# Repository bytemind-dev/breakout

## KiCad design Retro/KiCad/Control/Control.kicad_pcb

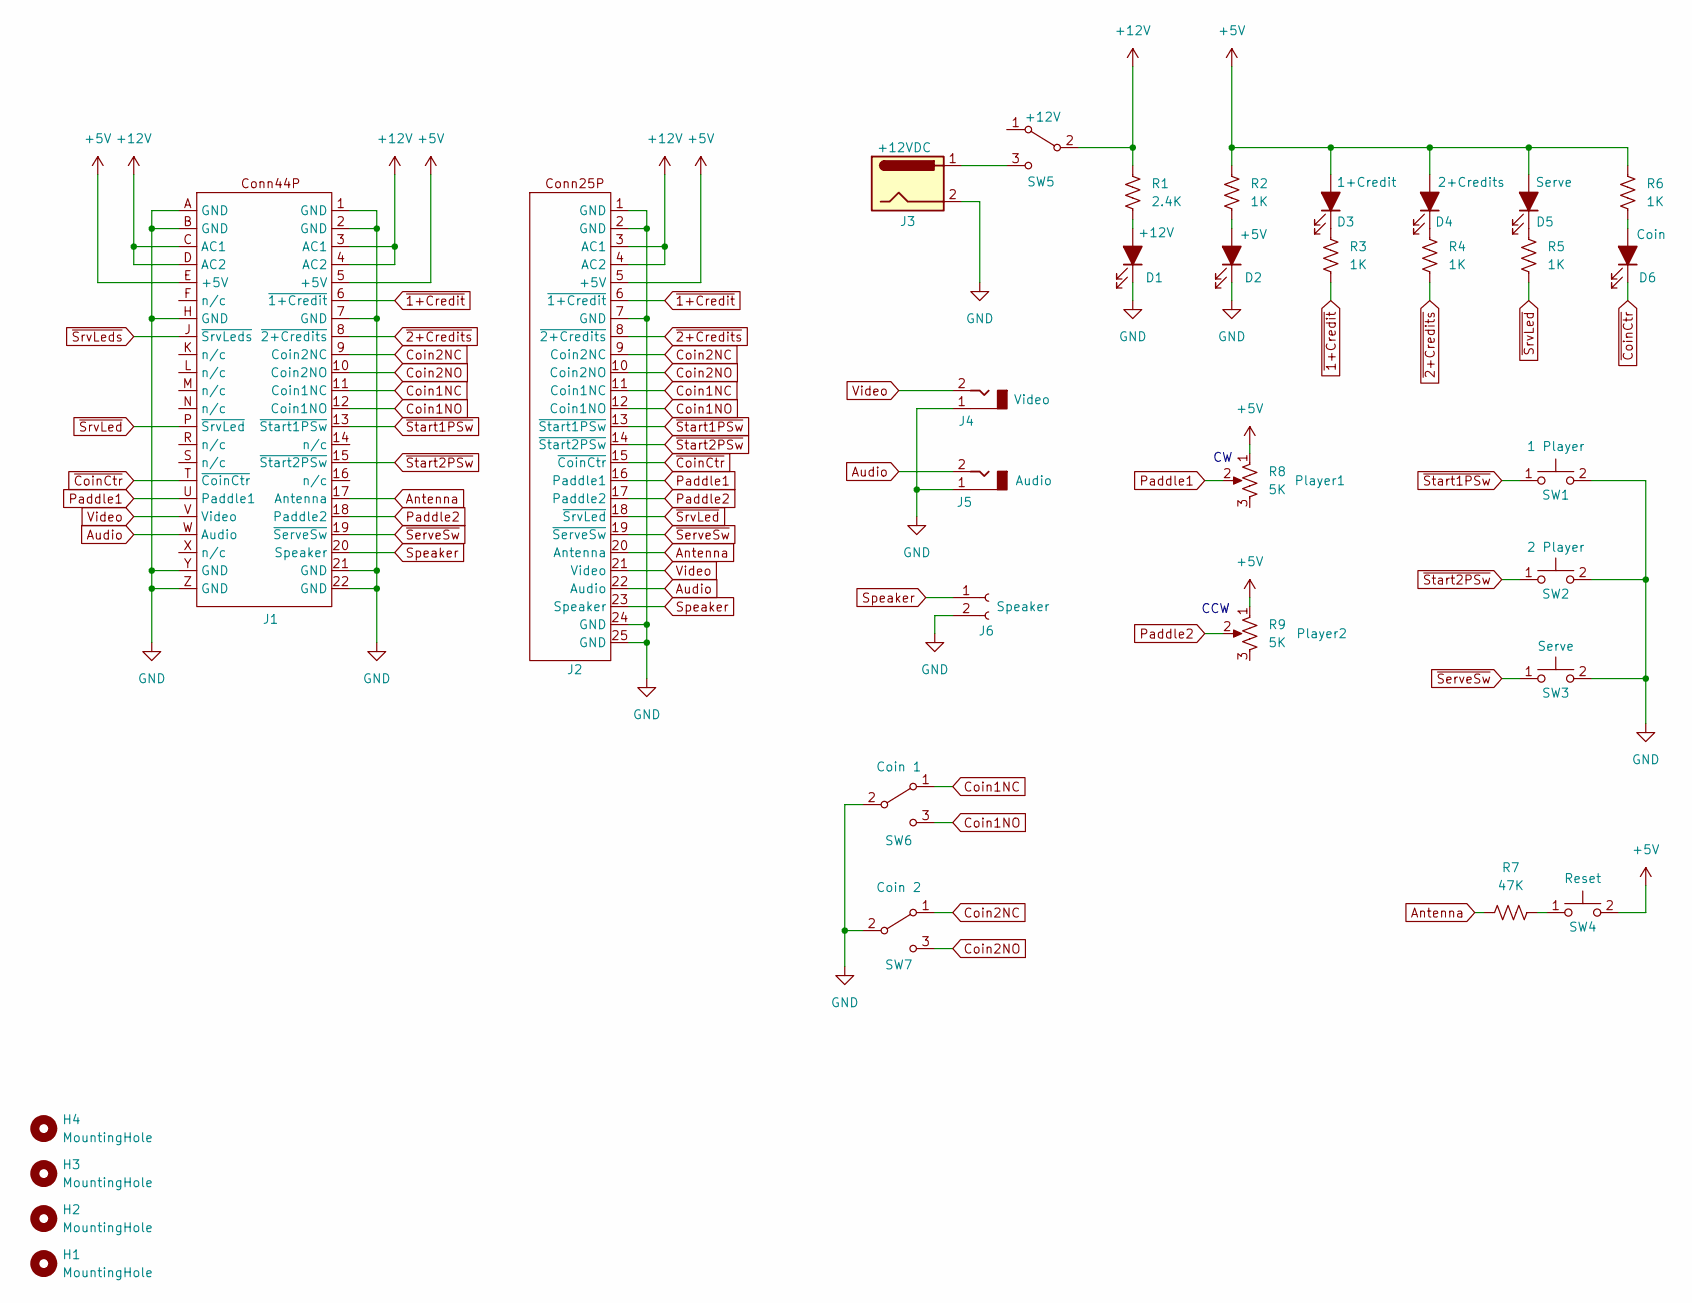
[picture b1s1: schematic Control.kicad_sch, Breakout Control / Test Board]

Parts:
D1: +12V; LED_D5.0mm
D2: +5V; LED_D5.0mm
D3: 1+Credit; LED_D5.0mm
D4: 2+Credits; LED_D5.0mm
D5: Serve; LED_D5.0mm
D6: Coin; LED_D5.0mm
H1, H2, H3, H4: MountingHole; Hole_4.3mm_M4
J1: Conn44F
J2: Conn_Head_1x25_P2.54mm_Vert
J3: Jack-DC; BarrelJack_Horizontal
J4: Video; CUI_RCJ-045
J5: Audio; CUI_RCJ-045
J6: Conn-TermBlock-2P
R1: 2.4K; R_Axial_0.6in
R2, R3, R4, R5, R6: 1K; R_Axial_0.6in
R7: 47K; R_Axial_0.6in
R8, R9: 5K; R_POT_Bourns_PDB181-A
SW1, SW2, SW3, SW4: SW_Push; SW_TACT_6.5x4.5mm
SW5, SW6, SW7: SW_SPDT; SW_Toggle_Gemini_A

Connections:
+5V: D3.2 (A), D4.2 (A), D5.2 (A), J1.5 (+5V), J1.E (+5V), J2.5 (+5V), R2.1, R6.1, R8.1, R9.1, SW4.2 (D)
+12V: J1.3 (AC1), J1.4 (AC2), J1.C (AC1), J1.D (AC2), J2.3 (AC1), J2.4 (AC2), R1.1, SW5.2 (B)
Antenna: J1.17 (Antenna), J2.20 (Antenna), R7.1
Audio: J1.W (Audio), J2.22 (Audio), J5.2
Coin1NC: J1.11 (Coin1NC), J2.11 (Coin1NC), SW6.1 (A)
Coin1NO: J1.12 (Coin1NO), J2.12 (Coin1NO), SW6.3 (C)
Coin2NC: J1.9 (Coin2NC), J2.9 (Coin2NC), SW7.1 (A)
Coin2NO: J1.10 (Coin2NO), J2.10 (Coin2NO), SW7.3 (C)
GND: D1.1 (K), D2.1 (K), J1.1 (GND), J1.2 (GND), J1.7 (GND), J1.21 (GND), J1.22 (GND), J1.A (GND), J1.B (GND), J1.H (GND), J1.Y (GND), J1.Z (GND), J2.1 (GND), J2.2 (GND), J2.7 (GND), J2.24 (GND), J2.25 (GND), J3.2, J4.1, J5.1, J6.2, SW1.2 (D), SW2.2 (D), SW3.2 (D), SW6.2 (B), SW7.2 (B)
unnamed: D1.2 (A), R1.2
unnamed: D2.2 (A), R2.2
unnamed: D3.1 (K), R3.1
unnamed: D4.1 (K), R4.1
unnamed: D5.1 (K), R5.1
unnamed: D6.2 (A), R6.2
unnamed: R7.2, SW4.1 (C)
unnamed: J3.1, SW5.3 (C)
Paddle1: J1.U (Paddle1), J2.16 (Paddle1), R8.2
Paddle2: J1.18 (Paddle2), J2.17 (Paddle2), R9.2
Speaker: J1.20 (Speaker), J2.23 (Speaker), J6.1
Video: J1.V (Video), J2.21 (Video), J4.2
~1+Credit: J1.6 (~1+Credit), J2.6 (~1+Credit), R3.2
~2+Credits: J1.8 (~2+Credits), J2.8 (~2+Credits), R4.2
~CoinCtr: D6.1 (K), J1.T (~CoinCtr), J2.15 (~CoinCtr)
~ServeSw: J1.19 (~ServeSw), J2.19 (~ServeSw), SW3.1 (C)
~SrvLeds: J1.J (~SrvLeds)
~SrvLed: J1.P (~SrvLed), J2.18 (~SrvLed), R5.2
~Start1PSw: J1.13 (~Start1PSw), J2.13 (~Start1PSw), SW1.1 (C)
~Start2PSw: J1.15 (~Start2PSw), J2.14 (~Start2PSw), SW2.1 (C)

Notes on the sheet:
CCW

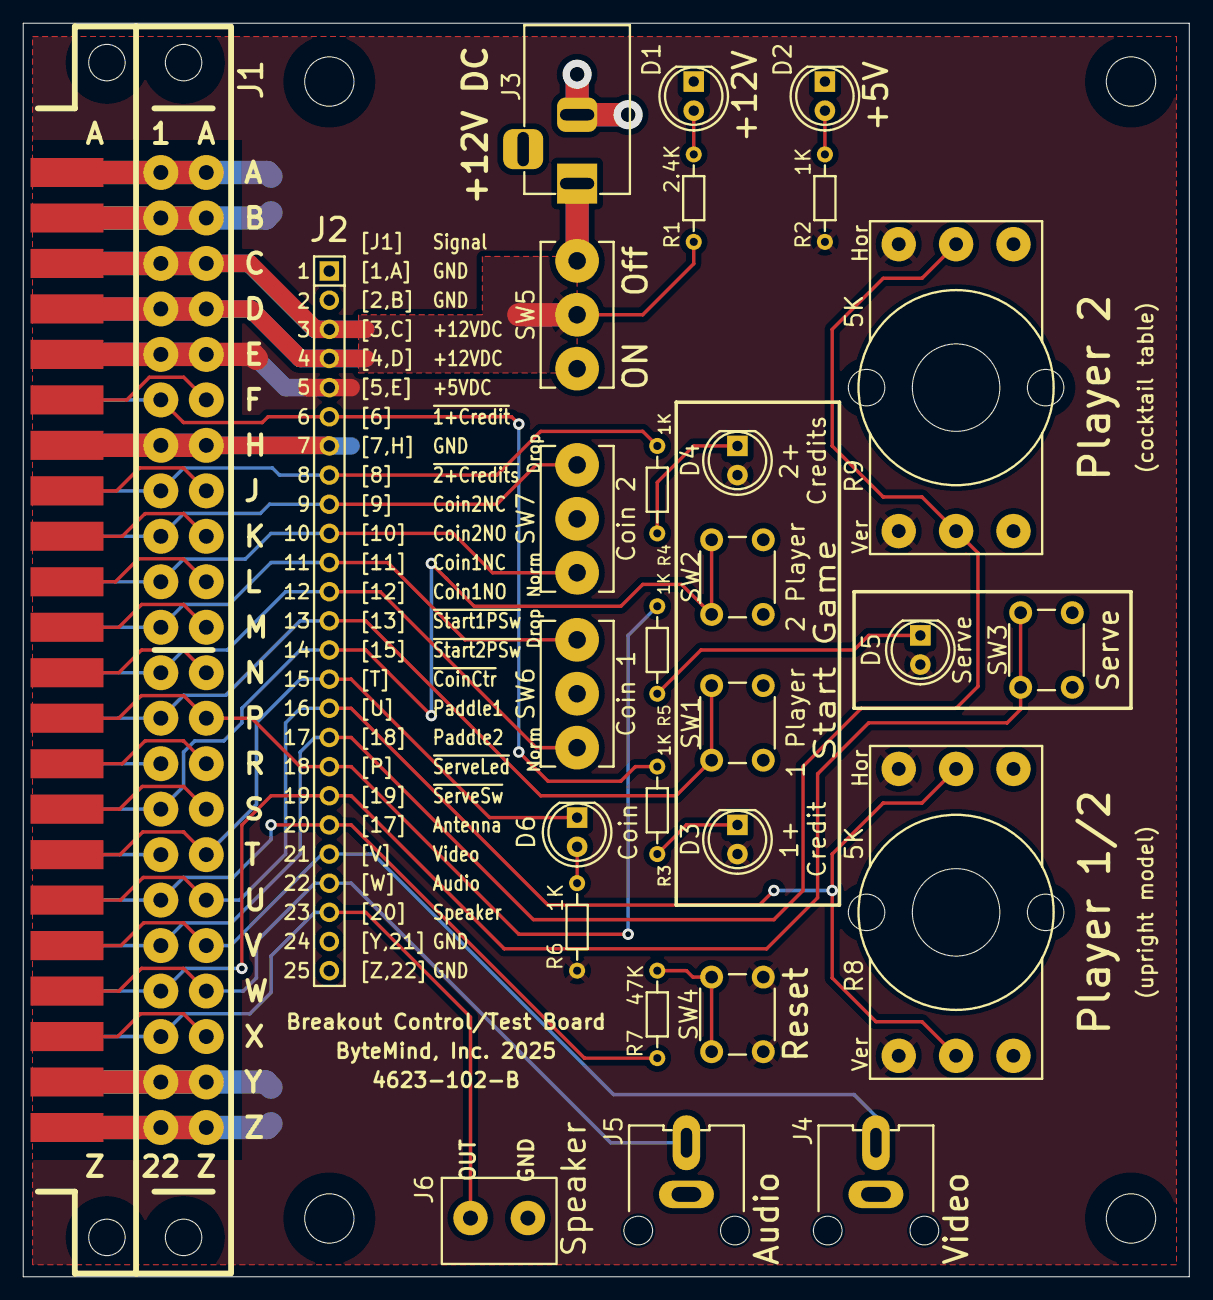
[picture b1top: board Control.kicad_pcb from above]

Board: 2 copper layers, 101.6 x 109.2 mm, 32 parts (0 on the bottom side), 28 nets.

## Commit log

2024-08-15 Initial Upload
2024-08-15 Folder Rename
2024-12-02 Image Upload
2024-12-22 Retro Breakout Part 2 Files
2024-12-22 Part 2 File Rename
2025-02-04 Retro Breakout Part 4 Files
2025-12-13 Add Rep7448 PLD script and binary.
2025-12-22 Post Part#25 Load
